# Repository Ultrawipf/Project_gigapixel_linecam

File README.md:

# Project Gigapixel
This repo contains code related to the "Project Gigapixel" linear scanning camera project.

It is designed for the sensor boards found in Epson v200/v30(0)/v37(0) scanners.

### Project video
Watch the build process:

### Info
There is no guarantee any of it works in other applications.
It is a work in progress and this repo is likely not enough to recreate this project on its own.
For inquiries contact me via the contact info in my [Github profile](https://github.com/Ultrawipf).

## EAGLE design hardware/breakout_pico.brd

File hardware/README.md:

### Hardware

Info: The hardware is very experimental and required modifications therefore no production files are shared and should only be used as an example reference.

The clock filters do require manual tuning and possibly pin adjustments in software and hardware.

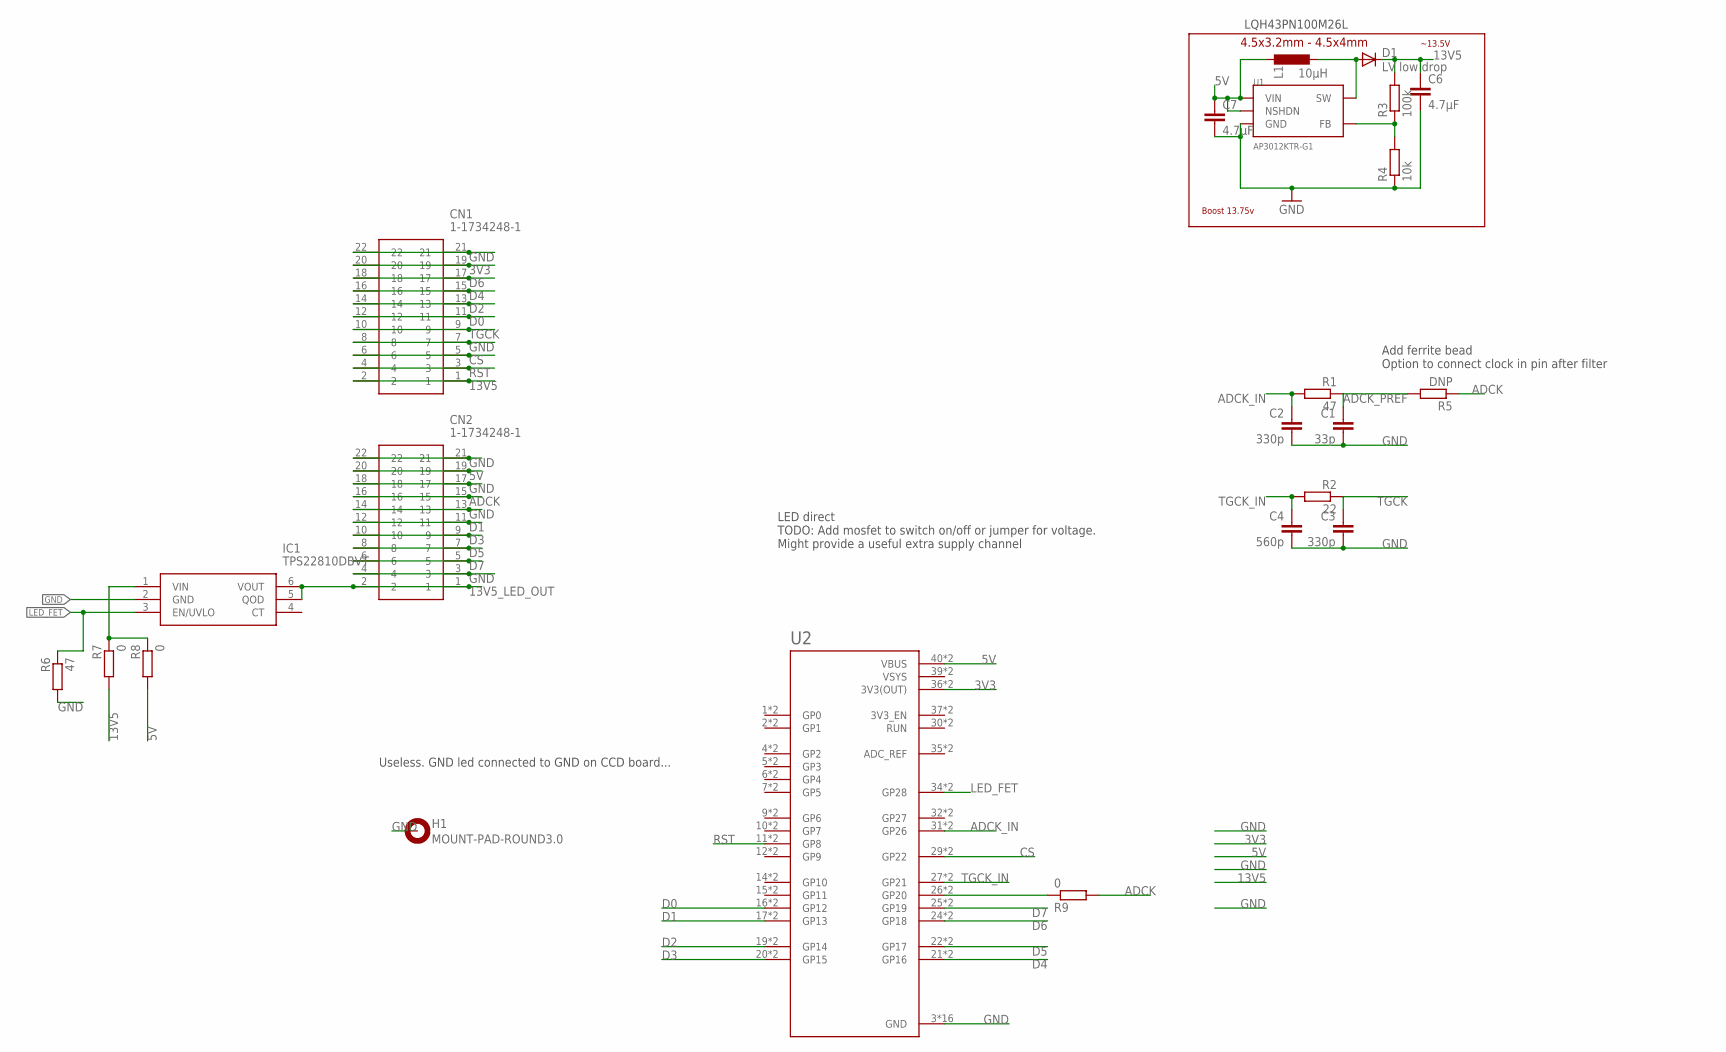
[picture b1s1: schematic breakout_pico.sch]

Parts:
C1: 33p; C0603
C2, C3: 330p; C0603
C4: 560p; C0603
C6, C7: 4.7µF; C0805
CN1, CN2: 1-1734248-1; 117342481
D1: LV low drop; SOD-123FL
H1: MOUNT-PAD-ROUND3.0; 3,0-PAD
IC1: TPS22810DBVT; SOT95P280X145-6N
L1: 10µH; L4532P
R1, R6: 47; R0603
R2: 22; R0603
R3: 100k; R0603
R4: 10k; R0603
R5: DNP; R0603
R7, R8, R9: 0; R0603
U1: AP3012KTR-G1; SOT23-5L
U2: RASPBERRY_PICO-NO_DEBUG; PICO-PKG-NO_DEBUG

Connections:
3V3: CN1.19, CN1.20, U2.36 (3V3(OUT)), U2.P$36 (3V3(OUT))
5V: C7.1, CN2.19, CN2.20, L1.1, R8.2, U1.4 (NSHDN), U1.5 (VIN), U2.40 (VBUS), U2.P$40 (VBUS)
13V5: C6.1, CN1.1, CN1.2, D1.C, R3.2, R7.2
13V5_LED_OUT: CN2.1, CN2.2, IC1.5 (QOD), IC1.6 (VOUT)
ADCK: CN2.15, CN2.16, R5.1, R9.2
ADCK_IN: C2.1, R1.2, U2.31 (GP26), U2.P$31 (GP26)
ADCK_PREF: C1.1, R1.1, R5.2
CS: CN1.5, CN1.6, U2.29 (GP22), U2.P$29 (GP22)
D0: CN1.11, CN1.12, U2.16 (GP12), U2.P$16 (GP12)
D1: CN2.11, CN2.12, U2.17 (GP13), U2.P$17 (GP13)
D2: CN1.13, CN1.14, U2.19 (GP14), U2.P$19 (GP14)
D3: CN2.9, CN2.10, U2.20 (GP15), U2.P$20 (GP15)
D4: CN1.15, CN1.16, U2.21 (GP16), U2.P$21 (GP16)
D5: CN2.7, CN2.8, U2.22 (GP17), U2.P$22 (GP17)
D6: CN1.17, CN1.18, U2.24 (GP18), U2.P$24 (GP18)
D7: CN2.5, CN2.6, U2.25 (GP19), U2.P$25 (GP19)
GND: C1.2, C2.2, C3.2, C4.2, C6.2, C7.2, CN1.7, CN1.8, CN1.21, CN1.22, CN2.3, CN2.4, CN2.13, CN2.14, CN2.17, CN2.18, CN2.21, CN2.22, H1.B3,0, IC1.2 (GND), R4.1, R6.2, U1.2 (GND), U2.3 (GND), U2.8 (GND), U2.13 (GND), U2.18 (GND), U2.23 (GND), U2.28 (GND), U2.33 (GND), U2.38 (GND), U2.P$3 (GND), U2.P$8 (GND), U2.P$13 (GND), U2.P$18 (GND), U2.P$23 (GND), U2.P$28 (GND), U2.P$33 (GND), U2.P$38 (GND)
LED_FET: IC1.3 (EN/UVLO), R6.1, U2.34 (GP28), U2.P$34 (GP28)
unnamed: R9.1, U2.26 (GP20), U2.P$26 (GP20)
unnamed: R3.1, R4.2, U1.3 (FB)
unnamed: D1.A, L1.2, U1.1 (SW)
unnamed: IC1.1 (VIN), R7.1, R8.1
RST: CN1.3, CN1.4, U2.11 (GP8), U2.P$11 (GP8)
TGCK: C3.1, CN1.9, CN1.10, R2.1
TGCK_IN: C4.1, R2.2, U2.27 (GP21), U2.P$27 (GP21)
VSYS: U2.39 (VSYS), U2.P$39 (VSYS)

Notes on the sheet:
Boost 13.75v
~13.5V
4.5x3.2mm - 4.5x4mm
LQH43PN100M26L
LED direct TODO: Add mosfet to switch on/off or jumper for voltage. Might provide a useful extra supply channel
Add ferrite bead Option to connect clock in pin after filter
Useless. GND led connected to GND on CCD board...

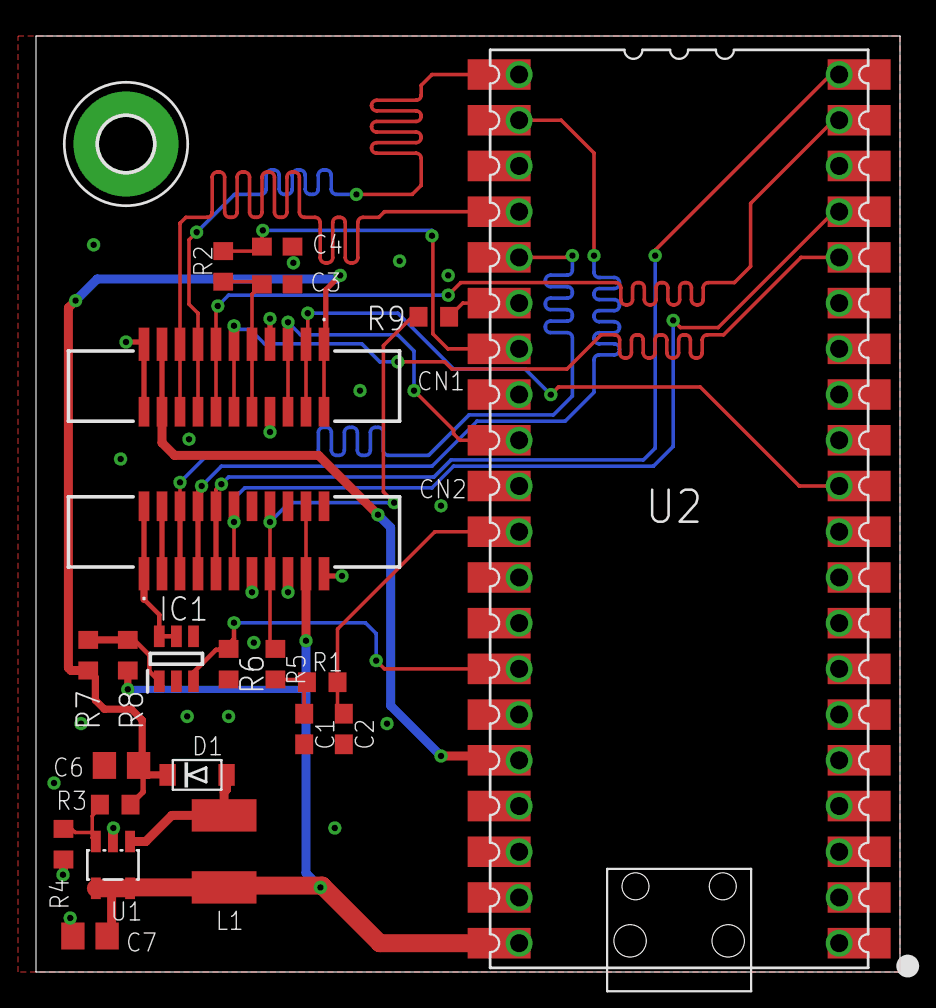
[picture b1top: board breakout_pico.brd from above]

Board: 2 copper layers, 48.0 x 52.0 mm, 23 parts (0 on the bottom side), 26 nets.

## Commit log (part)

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2025-05-09 Test files
2025-05-16 Add pi low level project. Add tmc2209 comms
2025-05-17 Restructured project
2025-05-17 Debug menu working
2025-05-20 Preview camera working
2025-05-20 Added run script + stuff
2025-05-21 Initial CCD tests
2025-07-01 Pi5 working!
2025-07-03 Corrected direction, pixel pitch and test program
2025-07-21 TG working
2025-07-22 Working on pi, base offsets
2025-07-23 Config and basic offset corrections working
2025-07-24 png working
2025-08-07 Preview working
2025-08-09 External buttons working
2025-08-11 Image view w. pinch zoom
2025-08-20 Test png reencoding
2025-08-21 Tuning, motor limits, usability
2025-08-31 12 line offset fix
2025-09-02 Line offset tests
2025-09-03 Gallery
2025-09-03 Motor fix
2025-09-05 Exposurecontrol?
2025-09-06 Line cam mode
2025-09-25 Added image info in gallery
2025-11-06 Disable png compression in 1/4 and higher res
2025-12-29 Subline + Exposure update
2026-01-27 UI Update
2026-01-27 Removed old files
2026-01-27 Initialize README
    Add README with project details and video link
2026-03-16 Added some hardware files
